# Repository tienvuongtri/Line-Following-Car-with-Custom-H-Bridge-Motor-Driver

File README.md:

# ESP32 Line-Following Robot with Custom H-Bridge

An autonomous and Bluetooth-controlled 4WD robot featuring a custom-designed H-Bridge motor driver, ultrasonic obstacle detection, and PID-based line tracking.

## 🛠️ Hardware Overview

* **Microcontroller:** ESP32 Development Board
* **Motor Driver:** Custom-designed L298N H-Bridge PCB
* **Line Sensor:** 5-Channel IR Sensor Array (Active Low logic)
* **Obstacle Detection:** HC-SR04 Ultrasonic Sensor
* **Actuators/Indicators:** 4x DC Motors, Buzzer, LED Indicator
* **Communication:** Bluetooth Classic (`ESP32_PRO_CAR`)

## 📍 Pin Mapping

| Component | ESP32 Pin | Component | ESP32 Pin |
| :--- | :--- | :--- | :--- |
| **Motor ENA** | GPIO 14 | **Sensor S1 (Far Left)** | GPIO 17 |
| **Motor ENB** | GPIO 32 | **Sensor S2 (Mid Left)** | GPIO 19 |
| **Motor IN1** | GPIO 27 | **Sensor S3 (Center)** | GPIO 4 |
| **Motor IN2** | GPIO 26 | **Sensor S4 (Mid Right)** | GPIO 16 |
| **Motor IN3** | GPIO 25 | **Sensor S5 (Far Right)**| GPIO 23 |
| **Motor IN4** | GPIO 33 | **Ultrasonic TRIG** | GPIO 5 |
| **Buzzer** | GPIO 15 | **Ultrasonic ECHO** | GPIO 18 |
| **LED** | GPIO 2 | | |

## 📂 Project Structure

* `xe_do_line_IC2005_G1/`: Arduino source code containing the PID algorithm, Bluetooth control logic, and sensor reading functions.
* `H-Bridge Module/`: KiCad 9 hardware design files, including schematics, PCB layout, and Gerber files for manufacturing the custom motor driver.
* `images/`: Real-world photos and 3D renderings of the hardware.

## 📸 Demonstration

**Custom H-Bridge PCB Design:**
<div align="center">

</div>

**Robot Assembly:**
<div align="center">

</div>

## ⚙️ Features & Operation Modes

The system operates in two main modes, switchable via a custom Bluetooth serial application:

1.  **Line Following Mode (Mode 1):** Uses a PID control loop optimized with a dynamic time delta (`dt`) to track lines smoothly. Features pre-programmed intersection handling and step counting.
2.  **Manual / Bluetooth Mode (Mode 2):** Allows remote directional control with automatic forward obstacle detection (stops and alerts via buzzer/LED if an object is closer than 8 cm).

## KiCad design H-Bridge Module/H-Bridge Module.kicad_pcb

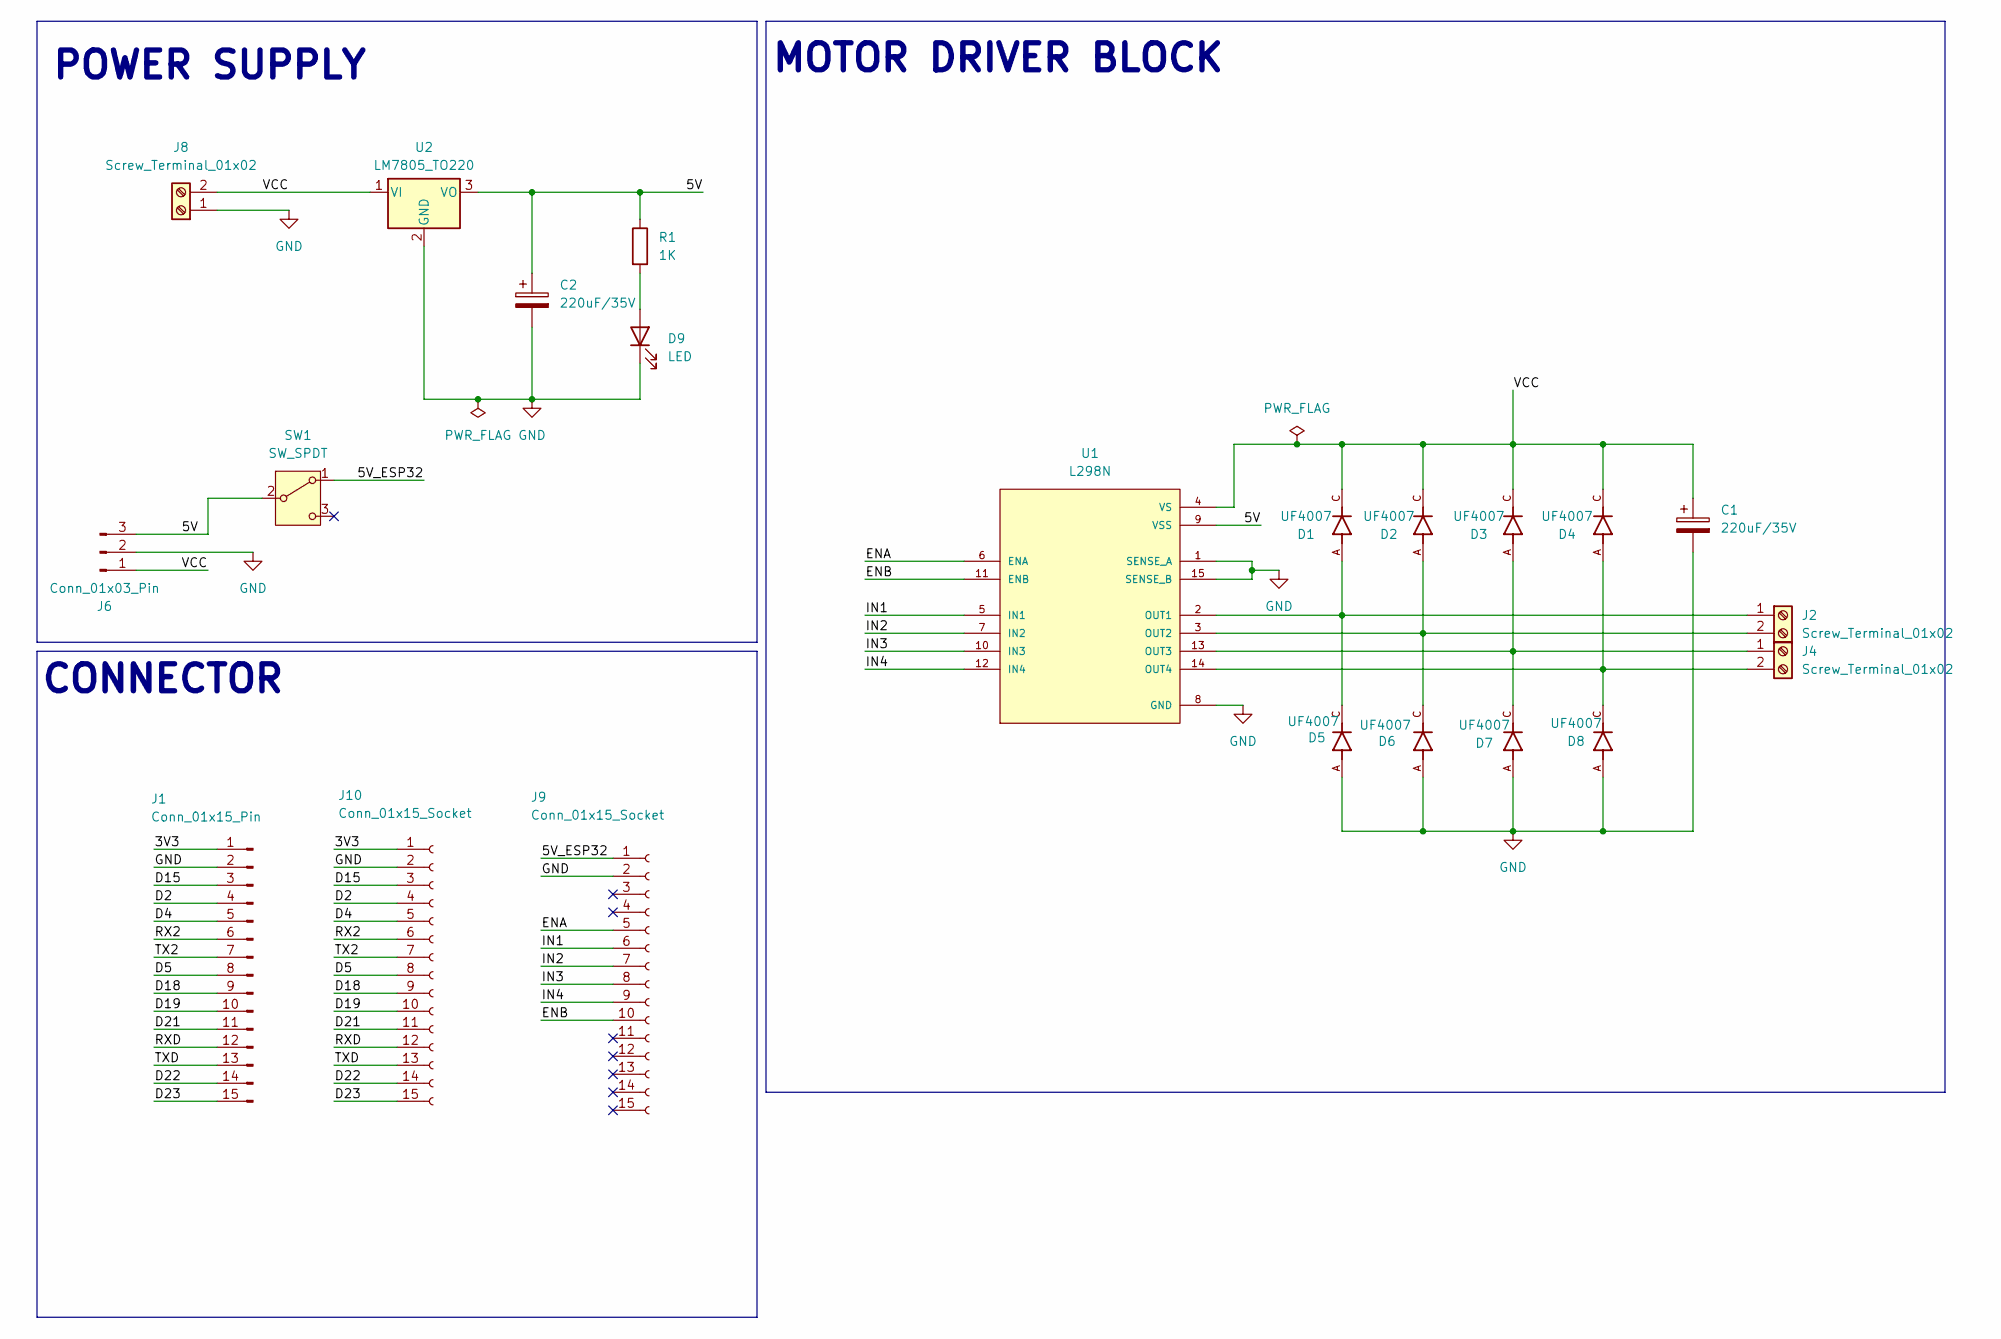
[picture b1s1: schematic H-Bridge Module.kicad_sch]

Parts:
C1, C2: 220uF/35V; CP_Radial_D8.0mm_P3.50mm
D1, D2, D3, D4, D5, D6, D7, D8: UF4007; DIOAD1036W78L470D235; PARTREV P2104
D9: LED; LED_D5.0mm
J1: Conn_01x15_Pin; PinHeader_1x15_P2.54mm_Vertical
J2, J4, J8: Screw_Terminal_01x02; TerminalBlock_Phoenix_MKDS-1,5-2-5.08_1x02_P5.08mm_Horizont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
J6: Conn_01x03_Pin; PinHeader_1x03_P2.54mm_Vertical
J9, J10: Conn_01x15_Socket; PinSocket_1x15_P2.54mm_Vertical
R1: 1K; R_Axial_DIN0207_L6.3mm_D2.5mm_P10.16mm_Horizontal
SW1: SW_SPDT; SW_Slide-03_Wuerth-WS-SLTV_10x2.5x6.4_P2.54mm
U1: L298N; TO127P2020X500X2100-15
U2: LM7805_TO220; TO-220-3_Vertical

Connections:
/3V3: J1.1, J10.1
/5V: C2.1, J6.3, R1.1, SW1.2 (B), U1.9 (VSS), U2.3 (VO)
/5V_ESP32: J9.1, SW1.1 (A)
/D2: J1.4, J10.4
/D4: J1.5, J10.5
/D5: J1.8, J10.8
/D15: J1.3, J10.3
/D18: J1.9, J10.9
/D19: J1.10, J10.10
/D21: J1.11, J10.11
/D22: J1.14, J10.14
/D23: J1.15, J10.15
/ENA: J9.5, U1.6 (ENA)
/ENB: J9.10, U1.11 (ENB)
/IN1: J9.6, U1.5 (IN1)
/IN2: J9.7, U1.7 (IN2)
/IN3: J9.8, U1.10 (IN3)
/IN4: J9.9, U1.12 (IN4)
/RX2: J1.6, J10.6
/RXD: J1.12, J10.12
/TX2: J1.7, J10.7
/TXD: J1.13, J10.13
/VCC: C1.1, D1.C, D2.C, D3.C, D4.C, J6.1, J8.2, U1.4 (VS), U2.1 (VI)
GND: C1.2, C2.2, D5.A, D6.A, D7.A, D8.A, D9.1 (K), J1.2, J6.2, J8.1, J9.2, J10.2, U1.1 (SENSE_A), U1.8 (GND), U1.15 (SENSE_B), U2.2 (GND)
unnamed: D9.2 (A), R1.2
unnamed: D1.A, D5.C, J2.1, U1.2 (OUT1)
unnamed: D2.A, D6.C, J2.2, U1.3 (OUT2)
unnamed: D3.A, D7.C, J4.1, U1.13 (OUT3)
unnamed: D4.A, D8.C, J4.2, U1.14 (OUT4)

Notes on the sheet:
CONNECTOR
POWER SUPPLY
MOTOR DRIVER BLOCK

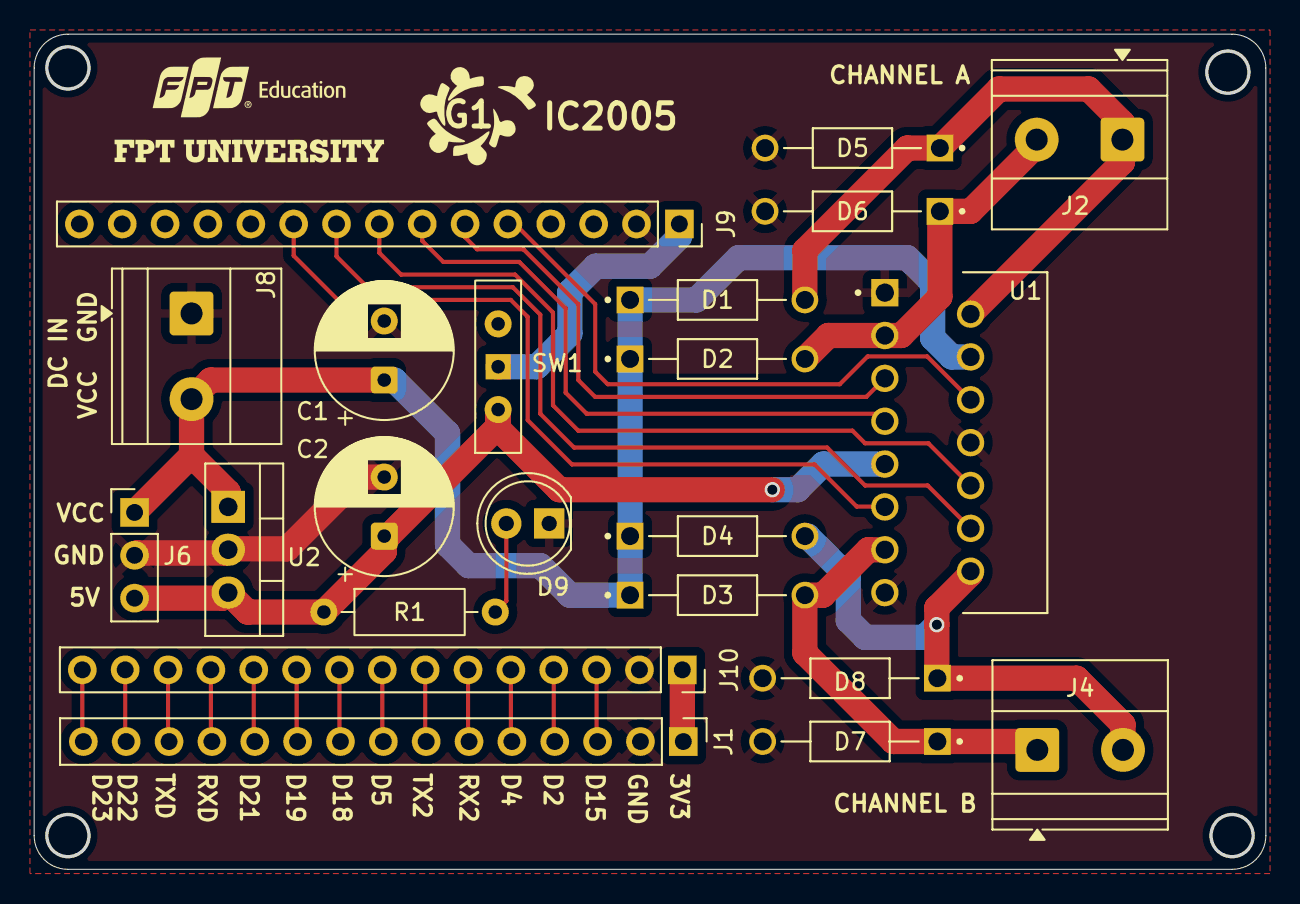
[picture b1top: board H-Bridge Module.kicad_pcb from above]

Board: 2 copper layers, 73.0 x 49.5 mm, 23 parts (0 on the bottom side), 29 nets.

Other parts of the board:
G1: LOGO; logo_G1
